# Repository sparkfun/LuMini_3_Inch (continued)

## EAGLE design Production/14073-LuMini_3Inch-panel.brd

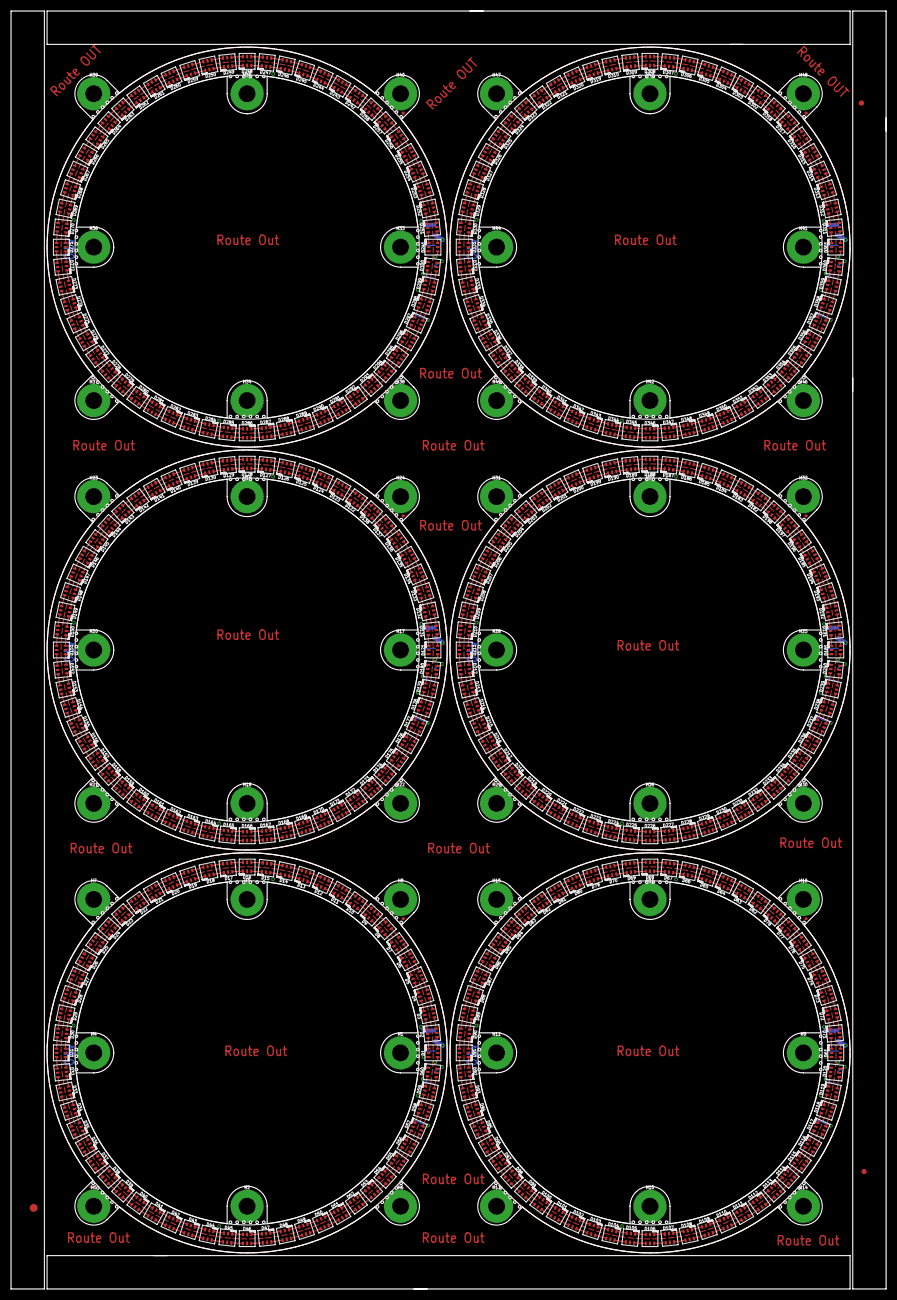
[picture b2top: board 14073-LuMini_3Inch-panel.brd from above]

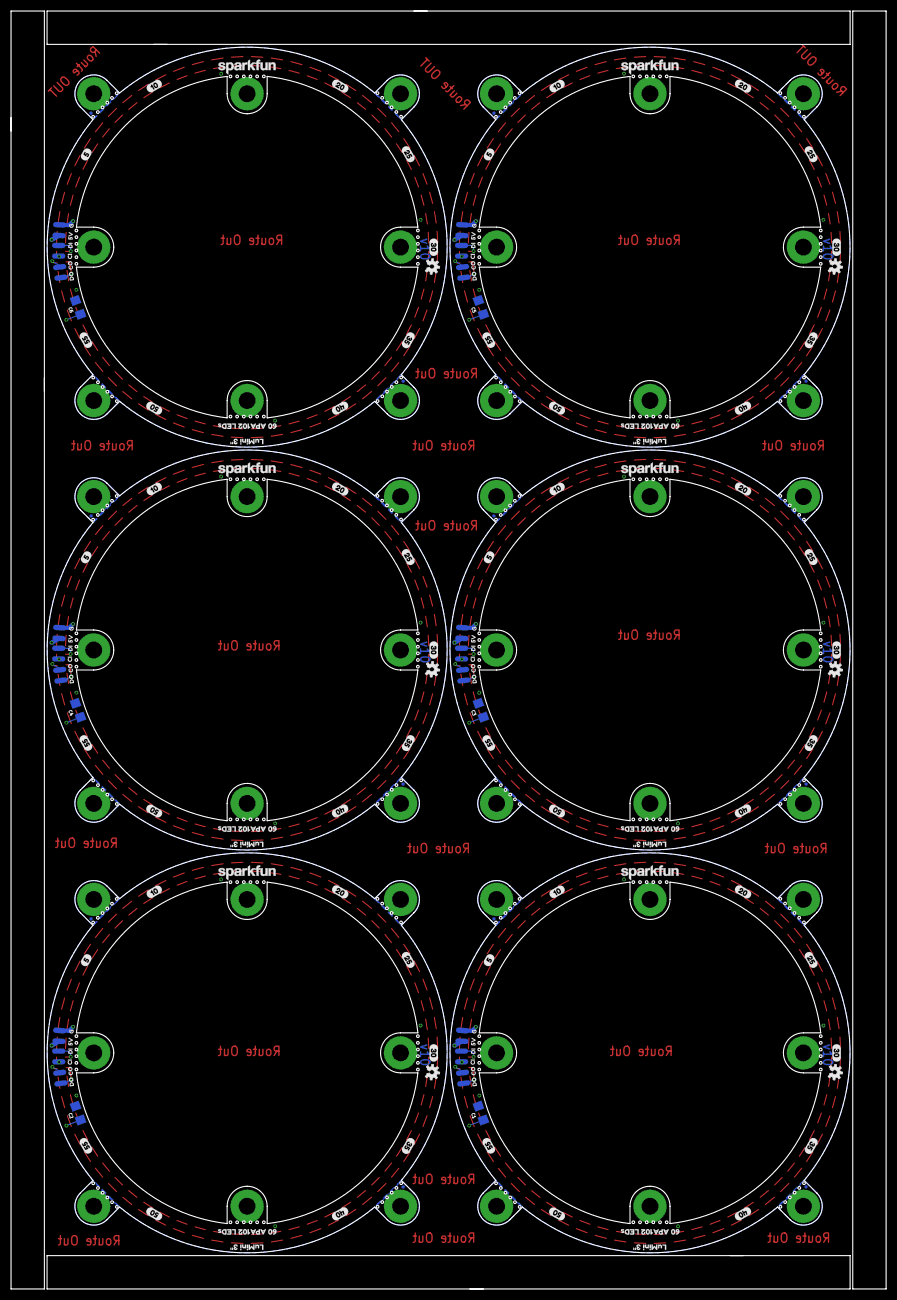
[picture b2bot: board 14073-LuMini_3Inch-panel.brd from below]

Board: 2 copper layers, 166.6 x 243.3 mm, 573 parts (150 on the bottom side), 744 nets.

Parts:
C1, C2, C3, C4, C5, C6: DNP; 1206
D1, D2, D3, D4, D5, D6, D7, D8, D9, D10, D11, D12, D13, D14, D15, D16, D17, D18, D19, D20, D21, D22, D23, D24, D25, D26, D27, D28, D29, D30, D31, D32, D33, D34, D35, D36, D37, D38, D39, D40, D41, D42, D43, D44, D45, D46, D47, D48, D49, D50, D51, D52, D53, D54, D55, D56, D57, D58, D59, D60, D61, D62, D63, D64, D65, D66, D67, D68, D69, D70, D71, D72, D73, D74, D75, D76, D77, D78, D79, D80, D81, D82, D83, D84, D85, D86, D87, D88, D89, D90, D91, D92, D93, D94, D95, D96, D97, D98, D99, D100, D101, D102, D103, D104, D105, D106, D107, D108, D109, D110, D111, D112, D113, D114, D115, D116, D117, D118, D119, D120, D121, D122, D123, D124, D125, D126, D127, D128, D129, D130, D131, D132, D133, D134, D135, D136, D137, D138, D139, D140, D141, D142, D143, D144, D145, D146, D147, D148, D149, D150, D151, D152, D153, D154, D155, D156, D157, D158, D159, D160, D161, D162, D163, D164, D165, D166, D167, D168, D169, D170, D171, D172, D173, D174, D175, D176, D177, D178, D179, D180, D181, D182, D183, D184, D185, D186, D187, D188, D189, D190, D191, D192, D193, D194, D195, D196, D197, D198, D199, D200, D201, D202, D203, D204, D205, D206, D207, D208, D209, D210, D211, D212, D213, D214, D215, D216, D217, D218, D219, D220, D221, D222, D223, D224, D225, D226, D227, D228, D229, D230, D231, D232, D233, D234, D235, D236, D237, D238, D239, D240, D241, D242, D243, D244, D245, D246, D247, D248, D249, D250, D251, D252, D253, D254, D255, D256, D257, D258, D259, D260, D261, D262, D263, D264, D265, D266, D267, D268, D269, D270, D271, D272, D273, D274, D275, D276, D277, D278, D279, D280, D281, D282, D283, D284, D285, D286, D287, D288, D289, D290, D291, D292, D293, D294, D295, D296, D297, D298, D299, D300, D301, D302, D303, D304, D305, D306, D307, D308, D309, D310, D311, D312, D313, D314, D315, D316, D317, D318, D319, D320, D321, D322, D323, D324, D325, D326, D327, D328, D329, D330, D331, D332, D333, D334, D335, D336, D337, D338, D339, D340, D341, D342, D343, D344, D345, D346, D347, D348, D349, D350, D351, D352, D353, D354, D355, D356, D357, D358, D359, D360: APA102-2020
E$6: FIDUCIAL-1.5X3
E$7, E$8: FIDUCIAL-1X2
FD1, FD2, FD3, FD4, FD5, FD6, FD7, FD8, FD9, FD10, FD11, FD12, FD13, FD14, FD15, FD16, FD17, FD18, FD19, FD20, FD21, FD22, FD23, FD24: FIDUCIALUFIDUCIAL; FIDUCIAL-MICRO
H1, H2, H3, H4, H5, H6, H7, H8, H9, H10, H11, H12, H13, H14, H15, H16, H17, H18, H19, H20, H21, H22, H23, H24, H25, H26, H27, H28, H29, H30, H31, H32, H33, H34, H35, H36, H37, H38, H39, H40, H41, H42, H43, H44, H45, H46, H47, H48: STANDOFF_ELECTRICAL-NOTHERMALS; STANDOFF-ELECTRICAL-NOTHERMALS
J1, J2, J3, J4, J5, J6, J7, J8, J9, J10, J11, J12, J13, J14, J15, J16, J17, J18: SOLDER_PAD_2
LOGO1, LOGO3, LOGO5, LOGO7, LOGO9, LOGO11: OSHW-LOGOS; OSHW-LOGO-S
LOGO2, LOGO4, LOGO6, LOGO8, LOGO10, LOGO12: SFE_LOGO_NAME.1_INCH; SFE_LOGO_NAME_.1
U$1, U$18, U$35, U$52, U$69, U$86: LUMINI_3#2
U$2, U$25, U$42, U$59, U$76, U$93: 60_APA102_LEDS0
U$3, U$26, U$43, U$60, U$77, U$94: 54
U$4, U$19, U$36, U$53, U$70, U$87: 5V6
U$5, U$20, U$37, U$54, U$71, U$88: G4
U$6, U$27, U$44, U$61, U$78, U$95: 105
U$7, U$21, U$38, U$55, U$72, U$89: DO3
U$8, U$22, U$39, U$56, U$73, U$90: CO1
U$9, U$23, U$40, U$57, U$74, U$91: CI6
U$10, U$24, U$41, U$58, U$75, U$92: DI4
U$11, U$28, U$45, U$62, U$79, U$96: 207
U$12, U$29, U$46, U$63, U$80, U$97: 258
U$13, U$30, U$47, U$64, U$81, U$98: 309
U$14, U$31, U$48, U$65, U$82, U$99: 3510
U$15, U$32, U$49, U$66, U$83, U$100: 4011
U$16, U$33, U$50, U$67, U$84, U$101: 5013
U$17, U$34, U$51, U$68, U$85, U$102: 5514

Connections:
5V: C1.1, D1.VDD, D2.VDD, D3.VDD, D4.VDD, D5.VDD, D6.VDD, D7.VDD, D8.VDD, D9.VDD, D10.VDD, D11.VDD, D12.VDD, D13.VDD, D14.VDD, D15.VDD, D16.VDD, D17.VDD, D18.VDD, D19.VDD, D20.VDD, D21.VDD, D22.VDD, D23.VDD, D24.VDD, D25.VDD, D26.VDD, D27.VDD, D28.VDD, D29.VDD, D30.VDD, D31.VDD, D32.VDD, D33.VDD, D34.VDD, D35.VDD, D36.VDD, D37.VDD, D38.VDD, D39.VDD, D40.VDD, D41.VDD, D42.VDD, D43.VDD, D44.VDD, D45.VDD, D46.VDD, D47.VDD, D48.VDD, D49.VDD, D50.VDD, D51.VDD, D52.VDD, D53.VDD, D54.VDD, D55.VDD, D56.VDD, D57.VDD, D58.VDD, D59.VDD, D60.VDD, J1.P$2
5V1: C2.1, D61.VDD, D62.VDD, D63.VDD, D64.VDD, D65.VDD, D66.VDD, D67.VDD, D68.VDD, D69.VDD, D70.VDD, D71.VDD, D72.VDD, D73.VDD, D74.VDD, D75.VDD, D76.VDD, D77.VDD, D78.VDD, D79.VDD, D80.VDD, D81.VDD, D82.VDD, D83.VDD, D84.VDD, D85.VDD, D86.VDD, D87.VDD, D88.VDD, D89.VDD, D90.VDD, D91.VDD, D92.VDD, D93.VDD, D94.VDD, D95.VDD, D96.VDD, D97.VDD, D98.VDD, D99.VDD, D100.VDD, D101.VDD, D102.VDD, D103.VDD, D104.VDD, D105.VDD, D106.VDD, D107.VDD, D108.VDD, D109.VDD, D110.VDD, D111.VDD, D112.VDD, D113.VDD, D114.VDD, D115.VDD, D116.VDD, D117.VDD, D118.VDD, D119.VDD, D120.VDD, J4.P$2
5V2: C3.1, D121.VDD, D122.VDD, D123.VDD, D124.VDD, D125.VDD, D126.VDD, D127.VDD, D128.VDD, D129.VDD, D130.VDD, D131.VDD, D132.VDD, D133.VDD, D134.VDD, D135.VDD, D136.VDD, D137.VDD, D138.VDD, D139.VDD, D140.VDD, D141.VDD, D142.VDD, D143.VDD, D144.VDD, D145.VDD, D146.VDD, D147.VDD, D148.VDD, D149.VDD, D150.VDD, D151.VDD, D152.VDD, D153.VDD, D154.VDD, D155.VDD, D156.VDD, D157.VDD, D158.VDD, D159.VDD, D160.VDD, D161.VDD, D162.VDD, D163.VDD, D164.VDD, D165.VDD, D166.VDD, D167.VDD, D168.VDD, D169.VDD, D170.VDD, D171.VDD, D172.VDD, D173.VDD, D174.VDD, D175.VDD, D176.VDD, D177.VDD, D178.VDD, D179.VDD, D180.VDD, J7.P$2
5V3: C4.1, D181.VDD, D182.VDD, D183.VDD, D184.VDD, D185.VDD, D186.VDD, D187.VDD, D188.VDD, D189.VDD, D190.VDD, D191.VDD, D192.VDD, D193.VDD, D194.VDD, D195.VDD, D196.VDD, D197.VDD, D198.VDD, D199.VDD, D200.VDD, D201.VDD, D202.VDD, D203.VDD, D204.VDD, D205.VDD, D206.VDD, D207.VDD, D208.VDD, D209.VDD, D210.VDD, D211.VDD, D212.VDD, D213.VDD, D214.VDD, D215.VDD, D216.VDD, D217.VDD, D218.VDD, D219.VDD, D220.VDD, D221.VDD, D222.VDD, D223.VDD, D224.VDD, D225.VDD, D226.VDD, D227.VDD, D228.VDD, D229.VDD, D230.VDD, D231.VDD, D232.VDD, D233.VDD, D234.VDD, D235.VDD, D236.VDD, D237.VDD, D238.VDD, D239.VDD, D240.VDD, J10.P$2
5V4: C5.1, D241.VDD, D242.VDD, D243.VDD, D244.VDD, D245.VDD, D246.VDD, D247.VDD, D248.VDD, D249.VDD, D250.VDD, D251.VDD, D252.VDD, D253.VDD, D254.VDD, D255.VDD, D256.VDD, D257.VDD, D258.VDD, D259.VDD, D260.VDD, D261.VDD, D262.VDD, D263.VDD, D264.VDD, D265.VDD, D266.VDD, D267.VDD, D268.VDD, D269.VDD, D270.VDD, D271.VDD, D272.VDD, D273.VDD, D274.VDD, D275.VDD, D276.VDD, D277.VDD, D278.VDD, D279.VDD, D280.VDD, D281.VDD, D282.VDD, D283.VDD, D284.VDD, D285.VDD, D286.VDD, D287.VDD, D288.VDD, D289.VDD, D290.VDD, D291.VDD, D292.VDD, D293.VDD, D294.VDD, D295.VDD, D296.VDD, D297.VDD, D298.VDD, D299.VDD, D300.VDD, J13.P$2
5V5: C6.1, D301.VDD, D302.VDD, D303.VDD, D304.VDD, D305.VDD, D306.VDD, D307.VDD, D308.VDD, D309.VDD, D310.VDD, D311.VDD, D312.VDD, D313.VDD, D314.VDD, D315.VDD, D316.VDD, D317.VDD, D318.VDD, D319.VDD, D320.VDD, D321.VDD, D322.VDD, D323.VDD, D324.VDD, D325.VDD, D326.VDD, D327.VDD, D328.VDD, D329.VDD, D330.VDD, D331.VDD, D332.VDD, D333.VDD, D334.VDD, D335.VDD, D336.VDD, D337.VDD, D338.VDD, D339.VDD, D340.VDD, D341.VDD, D342.VDD, D343.VDD, D344.VDD, D345.VDD, D346.VDD, D347.VDD, D348.VDD, D349.VDD, D350.VDD, D351.VDD, D352.VDD, D353.VDD, D354.VDD, D355.VDD, D356.VDD, D357.VDD, D358.VDD, D359.VDD, D360.VDD, J16.P$2
CI: D1.CKI, J2.P$2
CI1: D61.CKI, J5.P$2
CI2: D121.CKI, J8.P$2
CI3: D181.CKI, J11.P$2
CI4: D241.CKI, J14.P$2
CI5: D301.CKI, J17.P$2
CO: D60.CKO, J3.P$2
CO1: D120.CKO, J6.P$2
CO2: D180.CKO, J9.P$2
CO3: D240.CKO, J12.P$2
CO4: D300.CKO, J15.P$2
CO5: D360.CKO, J18.P$2
DI: D1.SDI, J2.P$1
DI1: D61.SDI, J5.P$1
DI2: D121.SDI, J8.P$1
DI3: D181.SDI, J11.P$1
DI4: D241.SDI, J14.P$1
DI5: D301.SDI, J17.P$1
DO: D60.SDO, J3.P$1
DO1: D120.SDO, J6.P$1
DO2: D180.SDO, J9.P$1
DO3: D240.SDO, J12.P$1
DO4: D300.SDO, J15.P$1
DO5: D360.SDO, J18.P$1
GND: C1.2, D1.GND, D2.GND, D3.GND, D4.GND, D5.GND, D6.GND, D7.GND, D8.GND, D9.GND, D10.GND, D11.GND, D12.GND, D13.GND, D14.GND, D15.GND, D16.GND, D17.GND, D18.GND, D19.GND, D20.GND, D21.GND, D22.GND, D23.GND, D24.GND, D25.GND, D26.GND, D27.GND, D28.GND, D29.GND, D30.GND, D31.GND, D32.GND, D33.GND, D34.GND, D35.GND, D36.GND, D37.GND, D38.GND, D39.GND, D40.GND, D41.GND, D42.GND, D43.GND, D44.GND, D45.GND, D46.GND, D47.GND, D48.GND, D49.GND, D50.GND, D51.GND, D52.GND, D53.GND, D54.GND, D55.GND, D56.GND, D57.GND, D58.GND, D59.GND, D60.GND, H1.P1, H2.P1, H3.P1, H4.P1, H5.P1, H6.P1, H7.P1, H8.P1, J1.P$1
GND1: C2.2, D61.GND, D62.GND, D63.GND, D64.GND, D65.GND, D66.GND, D67.GND, D68.GND, D69.GND, D70.GND, D71.GND, D72.GND, D73.GND, D74.GND, D75.GND, D76.GND, D77.GND, D78.GND, D79.GND, D80.GND, D81.GND, D82.GND, D83.GND, D84.GND, D85.GND, D86.GND, D87.GND, D88.GND, D89.GND, D90.GND, D91.GND, D92.GND, D93.GND, D94.GND, D95.GND, D96.GND, D97.GND, D98.GND, D99.GND, D100.GND, D101.GND, D102.GND, D103.GND, D104.GND, D105.GND, D106.GND, D107.GND, D108.GND, D109.GND, D110.GND, D111.GND, D112.GND, D113.GND, D114.GND, D115.GND, D116.GND, D117.GND, D118.GND, D119.GND, D120.GND, H9.P1, H10.P1, H11.P1, H12.P1, H13.P1, H14.P1, H15.P1, H16.P1, J4.P$1
GND2: C3.2, D121.GND, D122.GND, D123.GND, D124.GND, D125.GND, D126.GND, D127.GND, D128.GND, D129.GND, D130.GND, D131.GND, D132.GND, D133.GND, D134.GND, D135.GND, D136.GND, D137.GND, D138.GND, D139.GND, D140.GND, D141.GND, D142.GND, D143.GND, D144.GND, D145.GND, D146.GND, D147.GND, D148.GND, D149.GND, D150.GND, D151.GND, D152.GND, D153.GND, D154.GND, D155.GND, D156.GND, D157.GND, D158.GND, D159.GND, D160.GND, D161.GND, D162.GND, D163.GND, D164.GND, D165.GND, D166.GND, D167.GND, D168.GND, D169.GND, D170.GND, D171.GND, D172.GND, D173.GND, D174.GND, D175.GND, D176.GND, D177.GND, D178.GND, D179.GND, D180.GND, H17.P1, H18.P1, H19.P1, H20.P1, H21.P1, H22.P1, H23.P1, H24.P1, J7.P$1
GND3: C4.2, D181.GND, D182.GND, D183.GND, D184.GND, D185.GND, D186.GND, D187.GND, D188.GND, D189.GND, D190.GND, D191.GND, D192.GND, D193.GND, D194.GND, D195.GND, D196.GND, D197.GND, D198.GND, D199.GND, D200.GND, D201.GND, D202.GND, D203.GND, D204.GND, D205.GND, D206.GND, D207.GND, D208.GND, D209.GND, D210.GND, D211.GND, D212.GND, D213.GND, D214.GND, D215.GND, D216.GND, D217.GND, D218.GND, D219.GND, D220.GND, D221.GND, D222.GND, D223.GND, D224.GND, D225.GND, D226.GND, D227.GND, D228.GND, D229.GND, D230.GND, D231.GND, D232.GND, D233.GND, D234.GND, D235.GND, D236.GND, D237.GND, D238.GND, D239.GND, D240.GND, H25.P1, H26.P1, H27.P1, H28.P1, H29.P1, H30.P1, H31.P1, H32.P1, J10.P$1
GND4: C5.2, D241.GND, D242.GND, D243.GND, D244.GND, D245.GND, D246.GND, D247.GND, D248.GND, D249.GND, D250.GND, D251.GND, D252.GND, D253.GND, D254.GND, D255.GND, D256.GND, D257.GND, D258.GND, D259.GND, D260.GND, D261.GND, D262.GND, D263.GND, D264.GND, D265.GND, D266.GND, D267.GND, D268.GND, D269.GND, D270.GND, D271.GND, D272.GND, D273.GND, D274.GND, D275.GND, D276.GND, D277.GND, D278.GND, D279.GND, D280.GND, D281.GND, D282.GND, D283.GND, D284.GND, D285.GND, D286.GND, D287.GND, D288.GND, D289.GND, D290.GND, D291.GND, D292.GND, D293.GND, D294.GND, D295.GND, D296.GND, D297.GND, D298.GND, D299.GND, D300.GND, H33.P1, H34.P1, H35.P1, H36.P1, H37.P1, H38.P1, H39.P1, H40.P1, J13.P$1
GND5: C6.2, D301.GND, D302.GND, D303.GND, D304.GND, D305.GND, D306.GND, D307.GND, D308.GND, D309.GND, D310.GND, D311.GND, D312.GND, D313.GND, D314.GND, D315.GND, D316.GND, D317.GND, D318.GND, D319.GND, D320.GND, D321.GND, D322.GND, D323.GND, D324.GND, D325.GND, D326.GND, D327.GND, D328.GND, D329.GND, D330.GND, D331.GND, D332.GND, D333.GND, D334.GND, D335.GND, D336.GND, D337.GND, D338.GND, D339.GND, D340.GND, D341.GND, D342.GND, D343.GND, D344.GND, D345.GND, D346.GND, D347.GND, D348.GND, D349.GND, D350.GND, D351.GND, D352.GND, D353.GND, D354.GND, D355.GND, D356.GND, D357.GND, D358.GND, D359.GND, D360.GND, H41.P1, H42.P1, H43.P1, H44.P1, H45.P1, H46.P1, H47.P1, H48.P1, J16.P$1
unnamed: D4.CKO, D5.CKI
unnamed: D61.CKO, D71.CKI
unnamed: D61.SDO, D71.SDI
unnamed: D1.CKO, D2.CKI
unnamed: D1.SDO, D2.SDI
unnamed: D2.CKO, D3.CKI
unnamed: D2.SDO, D3.SDI
unnamed: D3.CKO, D4.CKI
unnamed: D3.SDO, D4.SDI
unnamed: D4.SDO, D5.SDI
unnamed: D5.CKO, D6.CKI
unnamed: D5.SDO, D6.SDI
unnamed: D6.CKO, D7.CKI
unnamed: D6.SDO, D7.SDI
unnamed: D7.CKO, D8.CKI
unnamed: D7.SDO, D8.SDI
unnamed: D16.SDO, D17.SDI
unnamed: D20.SDO, D21.SDI
unnamed: D9.CKO, D10.CKI
unnamed: D9.SDO, D10.SDI
unnamed: D10.CKO, D11.CKI
unnamed: D10.SDO, D11.SDI
unnamed: D11.CKO, D12.CKI
unnamed: D11.SDO, D12.SDI
unnamed: D12.CKO, D13.CKI
unnamed: D12.SDO, D13.SDI
unnamed: D13.CKO, D14.CKI
unnamed: D13.SDO, D14.SDI
unnamed: D14.CKO, D15.CKI
unnamed: D14.SDO, D15.SDI
unnamed: D45.CKO, D46.CKI
unnamed: D30.CKO, D31.CKI
unnamed: D8.CKO, D9.CKI
unnamed: D8.SDO, D9.SDI
unnamed: D17.CKO, D18.CKI
unnamed: D17.SDO, D18.SDI
unnamed: D18.CKO, D19.CKI
unnamed: D18.SDO, D19.SDI
unnamed: D19.CKO, D20.CKI
unnamed: D19.SDO, D20.SDI
unnamed: D30.SDO, D31.SDI
unnamed: D15.CKO, D16.CKI
unnamed: D16.CKO, D17.CKI
unnamed: D21.CKO, D22.CKI
unnamed: D21.SDO, D22.SDI
unnamed: D22.CKO, D23.CKI
unnamed: D22.SDO, D23.SDI
unnamed: D23.CKO, D24.CKI
unnamed: D23.SDO, D24.SDI
unnamed: D24.CKO, D25.CKI
unnamed: D24.SDO, D25.SDI
unnamed: D25.CKO, D26.CKI
unnamed: D25.SDO, D26.SDI
unnamed: D26.CKO, D27.CKI
unnamed: D26.SDO, D27.SDI
unnamed: D27.CKO, D28.CKI
unnamed: D27.SDO, D28.SDI
unnamed: D29.CKO, D30.CKI
unnamed: D29.SDO, D30.SDI
unnamed: D15.SDO, D16.SDI
unnamed: D45.SDO, D46.SDI
unnamed: D31.CKO, D32.CKI
unnamed: D31.SDO, D32.SDI
unnamed: D32.CKO, D33.CKI
unnamed: D32.SDO, D33.SDI
unnamed: D33.CKO, D34.CKI
unnamed: D33.SDO, D34.SDI
unnamed: D34.CKO, D35.CKI
unnamed: D34.SDO, D35.SDI
unnamed: D35.CKO, D36.CKI
unnamed: D35.SDO, D36.SDI
unnamed: D37.CKO, D38.CKI
unnamed: D37.SDO, D38.SDI
unnamed: D38.SDO, D39.SDI
unnamed: D39.CKO, D40.CKI
unnamed: D39.SDO, D40.SDI
unnamed: D38.CKO, D39.CKI
unnamed: D28.CKO, D29.CKI
unnamed: D28.SDO, D29.SDI
unnamed: D36.SDO, D37.SDI
unnamed: D36.CKO, D37.CKI
unnamed: D40.CKO, D41.CKI
unnamed: D40.SDO, D41.SDI
unnamed: D41.CKO, D42.CKI
unnamed: D41.SDO, D42.SDI
unnamed: D42.CKO, D43.CKI
unnamed: D42.SDO, D43.SDI
unnamed: D43.CKO, D44.CKI
unnamed: D43.SDO, D44.SDI
unnamed: D44.CKO, D45.CKI
unnamed: D44.SDO, D45.SDI
unnamed: D71.CKO, D72.CKI
unnamed: D71.SDO, D72.SDI
unnamed: D46.CKO, D47.CKI
unnamed: D46.SDO, D47.SDI
unnamed: D47.CKO, D48.CKI
unnamed: D47.SDO, D48.SDI
unnamed: D49.CKO, D50.CKI
unnamed: D49.SDO, D50.SDI
unnamed: D50.CKO, D51.CKI
unnamed: D50.SDO, D51.SDI
unnamed: D51.CKO, D52.CKI
unnamed: D51.SDO, D52.SDI
unnamed: D52.CKO, D53.CKI
unnamed: D52.SDO, D53.SDI
unnamed: D53.CKO, D54.CKI
unnamed: D53.SDO, D54.SDI
unnamed: D54.CKO, D55.CKI
unnamed: D54.SDO, D55.SDI
unnamed: D55.CKO, D56.CKI
unnamed: D55.SDO, D56.SDI
unnamed: D57.CKO, D58.CKI
unnamed: D57.SDO, D58.SDI
unnamed: D58.SDO, D59.SDI
unnamed: D59.CKO, D60.CKI
unnamed: D59.SDO, D60.SDI
unnamed: D58.CKO, D59.CKI
unnamed: D48.CKO, D49.CKI
unnamed: D48.SDO, D49.SDI
unnamed: D56.SDO, D57.SDI
unnamed: D56.CKO, D57.CKI
unnamed: D72.CKO, D73.CKI
unnamed: D72.SDO, D73.SDI
unnamed: D20.CKO, D21.CKI
unnamed: D73.CKO, D74.CKI
unnamed: D73.SDO, D74.SDI
unnamed: D74.CKO, D75.CKI
unnamed: D74.SDO, D75.SDI
unnamed: D75.CKO, D76.CKI
unnamed: D75.SDO, D76.SDI
unnamed: D76.CKO, D77.CKI
unnamed: D76.SDO, D77.SDI
unnamed: D62.CKI, D78.CKO
unnamed: D62.SDI, D78.SDO
unnamed: D62.CKO, D63.CKI
unnamed: D62.SDO, D63.SDI
unnamed: D63.CKO, D64.CKI
unnamed: D63.SDO, D64.SDI
unnamed: D64.CKO, D65.CKI
unnamed: D64.SDO, D65.SDI
unnamed: D65.CKO, D66.CKI
unnamed: D65.SDO, D66.SDI
unnamed: D66.CKO, D67.CKI
unnamed: D66.SDO, D67.SDI
unnamed: D69.CKO, D70.CKI
unnamed: D69.SDO, D70.SDI
unnamed: D70.SDO, D79.SDI
unnamed: D79.CKO, D80.CKI
unnamed: D79.SDO, D80.SDI
unnamed: D70.CKO, D79.CKI
unnamed: D77.CKO, D78.CKI
unnamed: D77.SDO, D78.SDI
unnamed: D68.SDO, D69.SDI
unnamed: D68.CKO, D69.CKI
unnamed: D81.CKO, D82.CKI
unnamed: D81.SDO, D82.SDI
unnamed: D82.CKO, D83.CKI
unnamed: D82.SDO, D83.SDI
unnamed: D83.CKO, D84.CKI
unnamed: D83.SDO, D84.SDI
unnamed: D84.CKO, D85.CKI
unnamed: D84.SDO, D85.SDI
unnamed: D85.CKO, D86.CKI
unnamed: D85.SDO, D86.SDI
unnamed: D86.CKO, D87.CKI
unnamed: D86.SDO, D87.SDI
unnamed: D87.CKO, D88.CKI
unnamed: D87.SDO, D88.SDI
unnamed: D89.CKO, D90.CKI
unnamed: D89.SDO, D90.SDI
unnamed: D91.CKO, D92.CKI
unnamed: D91.SDO, D92.SDI
unnamed: D92.CKO, D93.CKI
unnamed: D92.SDO, D93.SDI
unnamed: D93.CKO, D94.CKI
unnamed: D93.SDO, D94.SDI
unnamed: D94.CKO, D95.CKI
unnamed: D94.SDO, D95.SDI
unnamed: D95.CKO, D96.CKI
unnamed: D95.SDO, D96.SDI
unnamed: D97.CKO, D98.CKI
unnamed: D97.SDO, D98.SDI
unnamed: D98.SDO, D99.SDI
unnamed: D99.CKO, D100.CKI
unnamed: D99.SDO, D100.SDI
unnamed: D98.CKO, D99.CKI
unnamed: D88.CKO, D89.CKI
unnamed: D88.SDO, D89.SDI
unnamed: D96.SDO, D97.SDI
unnamed: D96.CKO, D97.CKI
unnamed: D101.CKO, D102.CKI
unnamed: D101.SDO, D102.SDI
unnamed: D102.CKO, D103.CKI
unnamed: D102.SDO, D103.SDI
unnamed: D103.CKO, D104.CKI
unnamed: D103.SDO, D104.SDI
unnamed: D104.CKO, D105.CKI
unnamed: D104.SDO, D105.SDI
unnamed: D106.CKO, D107.CKI
unnamed: D106.SDO, D107.SDI
unnamed: D107.CKO, D108.CKI
unnamed: D107.SDO, D108.SDI
unnamed: D109.CKO, D110.CKI
unnamed: D109.SDO, D110.SDI
unnamed: D110.CKO, D111.CKI
unnamed: D110.SDO, D111.SDI
unnamed: D111.CKO, D112.CKI
unnamed: D111.SDO, D112.SDI
unnamed: D112.CKO, D113.CKI
unnamed: D112.SDO, D113.SDI
unnamed: D113.CKO, D114.CKI
unnamed: D113.SDO, D114.SDI
unnamed: D114.CKO, D115.CKI
unnamed: D114.SDO, D115.SDI
unnamed: D115.CKO, D116.CKI
unnamed: D115.SDO, D116.SDI
unnamed: D117.CKO, D118.CKI
unnamed: D117.SDO, D118.SDI
unnamed: D118.SDO, D119.SDI
unnamed: D119.CKO, D120.CKI
unnamed: D119.SDO, D120.SDI
unnamed: D118.CKO, D119.CKI
unnamed: D108.CKO, D109.CKI
unnamed: D108.SDO, D109.SDI
unnamed: D116.SDO, D117.SDI
unnamed: D116.CKO, D117.CKI
unnamed: D80.CKO, D81.CKI
unnamed: D80.SDO, D81.SDI
unnamed: D105.CKO, D106.CKI
unnamed: D90.CKO, D91.CKI
unnamed: D90.SDO, D91.SDI
unnamed: D67.CKO, D68.CKI
unnamed: D67.SDO, D68.SDI
unnamed: D105.SDO, D106.SDI
unnamed: D100.CKO, D101.CKI
unnamed: D100.SDO, D101.SDI
unnamed: D121.CKO, D131.CKI
unnamed: D121.SDO, D131.SDI
unnamed: D131.CKO, D132.CKI
unnamed: D131.SDO, D132.SDI
unnamed: D132.CKO, D133.CKI
unnamed: D132.SDO, D133.SDI
unnamed: D133.CKO, D134.CKI
unnamed: D133.SDO, D134.SDI
unnamed: D134.CKO, D135.CKI
unnamed: D134.SDO, D135.SDI
unnamed: D135.CKO, D136.CKI
unnamed: D135.SDO, D136.SDI
unnamed: D136.CKO, D137.CKI
unnamed: D136.SDO, D137.SDI
unnamed: D122.CKI, D138.CKO
unnamed: D122.SDI, D138.SDO
unnamed: D122.CKO, D123.CKI
unnamed: D122.SDO, D123.SDI
unnamed: D123.CKO, D124.CKI
unnamed: D123.SDO, D124.SDI
unnamed: D124.CKO, D125.CKI
unnamed: D124.SDO, D125.SDI
unnamed: D125.CKO, D126.CKI
unnamed: D125.SDO, D126.SDI
unnamed: D126.CKO, D127.CKI
unnamed: D126.SDO, D127.SDI
unnamed: D129.CKO, D130.CKI
unnamed: D129.SDO, D130.SDI
unnamed: D130.SDO, D139.SDI
unnamed: D139.CKO, D140.CKI
unnamed: D139.SDO, D140.SDI
unnamed: D130.CKO, D139.CKI
unnamed: D137.CKO, D138.CKI
unnamed: D137.SDO, D138.SDI
unnamed: D128.SDO, D129.SDI
unnamed: D128.CKO, D129.CKI
unnamed: D141.CKO, D142.CKI
unnamed: D141.SDO, D142.SDI
unnamed: D142.CKO, D143.CKI
unnamed: D142.SDO, D143.SDI
unnamed: D143.CKO, D144.CKI
unnamed: D143.SDO, D144.SDI
unnamed: D144.CKO, D145.CKI
unnamed: D144.SDO, D145.SDI
unnamed: D145.CKO, D146.CKI
unnamed: D145.SDO, D146.SDI
unnamed: D146.CKO, D147.CKI
unnamed: D146.SDO, D147.SDI
unnamed: D147.CKO, D148.CKI
unnamed: D147.SDO, D148.SDI
unnamed: D149.CKO, D150.CKI
unnamed: D149.SDO, D150.SDI
unnamed: D151.CKO, D152.CKI
unnamed: D151.SDO, D152.SDI
unnamed: D152.CKO, D153.CKI
unnamed: D152.SDO, D153.SDI
unnamed: D153.CKO, D154.CKI
unnamed: D153.SDO, D154.SDI
unnamed: D154.CKO, D155.CKI
unnamed: D154.SDO, D155.SDI
unnamed: D155.CKO, D156.CKI
unnamed: D155.SDO, D156.SDI
unnamed: D157.CKO, D158.CKI
unnamed: D157.SDO, D158.SDI
unnamed: D158.SDO, D159.SDI
unnamed: D159.CKO, D160.CKI
unnamed: D159.SDO, D160.SDI
unnamed: D158.CKO, D159.CKI
unnamed: D148.CKO, D149.CKI
unnamed: D148.SDO, D149.SDI
unnamed: D156.SDO, D157.SDI
unnamed: D156.CKO, D157.CKI
unnamed: D161.CKO, D162.CKI
unnamed: D161.SDO, D162.SDI
unnamed: D162.CKO, D163.CKI
unnamed: D162.SDO, D163.SDI
unnamed: D163.CKO, D164.CKI
unnamed: D163.SDO, D164.SDI
unnamed: D164.CKO, D165.CKI
unnamed: D164.SDO, D165.SDI
unnamed: D166.CKO, D167.CKI
unnamed: D166.SDO, D167.SDI
unnamed: D167.CKO, D168.CKI
unnamed: D167.SDO, D168.SDI
unnamed: D169.CKO, D170.CKI
unnamed: D169.SDO, D170.SDI
unnamed: D170.CKO, D171.CKI
unnamed: D170.SDO, D171.SDI
unnamed: D171.CKO, D172.CKI
unnamed: D171.SDO, D172.SDI
unnamed: D172.CKO, D173.CKI
unnamed: D172.SDO, D173.SDI
unnamed: D173.CKO, D174.CKI
unnamed: D173.SDO, D174.SDI
unnamed: D174.CKO, D175.CKI
unnamed: D174.SDO, D175.SDI
unnamed: D175.CKO, D176.CKI
unnamed: D175.SDO, D176.SDI
unnamed: D177.CKO, D178.CKI
unnamed: D177.SDO, D178.SDI
unnamed: D178.SDO, D179.SDI
unnamed: D179.CKO, D180.CKI
unnamed: D179.SDO, D180.SDI
unnamed: D178.CKO, D179.CKI
unnamed: D168.CKO, D169.CKI
unnamed: D168.SDO, D169.SDI
unnamed: D176.SDO, D177.SDI
unnamed: D176.CKO, D177.CKI
unnamed: D140.CKO, D141.CKI
unnamed: D140.SDO, D141.SDI
unnamed: D165.CKO, D166.CKI
unnamed: D150.CKO, D151.CKI
unnamed: D150.SDO, D151.SDI
unnamed: D127.CKO, D128.CKI
unnamed: D127.SDO, D128.SDI
unnamed: D165.SDO, D166.SDI
unnamed: D160.CKO, D161.CKI
unnamed: D160.SDO, D161.SDI
unnamed: D181.CKO, D191.CKI
unnamed: D181.SDO, D191.SDI
unnamed: D191.CKO, D192.CKI
unnamed: D191.SDO, D192.SDI
unnamed: D192.CKO, D193.CKI
unnamed: D192.SDO, D193.SDI
unnamed: D193.CKO, D194.CKI
unnamed: D193.SDO, D194.SDI
unnamed: D194.CKO, D195.CKI
unnamed: D194.SDO, D195.SDI
unnamed: D195.CKO, D196.CKI
unnamed: D195.SDO, D196.SDI
unnamed: D196.CKO, D197.CKI
unnamed: D196.SDO, D197.SDI
unnamed: D182.CKI, D198.CKO
unnamed: D182.SDI, D198.SDO
unnamed: D182.CKO, D183.CKI
unnamed: D182.SDO, D183.SDI
unnamed: D183.CKO, D184.CKI
unnamed: D183.SDO, D184.SDI
unnamed: D184.CKO, D185.CKI
unnamed: D184.SDO, D185.SDI
unnamed: D185.CKO, D186.CKI
unnamed: D185.SDO, D186.SDI
unnamed: D186.CKO, D187.CKI
unnamed: D186.SDO, D187.SDI
unnamed: D189.CKO, D190.CKI
unnamed: D189.SDO, D190.SDI
unnamed: D190.SDO, D199.SDI
unnamed: D199.CKO, D200.CKI
unnamed: D199.SDO, D200.SDI
unnamed: D190.CKO, D199.CKI
unnamed: D197.CKO, D198.CKI
unnamed: D197.SDO, D198.SDI
unnamed: D188.SDO, D189.SDI
unnamed: D188.CKO, D189.CKI
unnamed: D201.CKO, D202.CKI
unnamed: D201.SDO, D202.SDI
unnamed: D202.CKO, D203.CKI
unnamed: D202.SDO, D203.SDI
unnamed: D203.CKO, D204.CKI
unnamed: D203.SDO, D204.SDI
unnamed: D204.CKO, D205.CKI
unnamed: D204.SDO, D205.SDI
unnamed: D205.CKO, D206.CKI
unnamed: D205.SDO, D206.SDI
unnamed: D206.CKO, D207.CKI
unnamed: D206.SDO, D207.SDI
unnamed: D207.CKO, D208.CKI
unnamed: D207.SDO, D208.SDI
unnamed: D209.CKO, D210.CKI
unnamed: D209.SDO, D210.SDI
unnamed: D211.CKO, D212.CKI
unnamed: D211.SDO, D212.SDI
unnamed: D212.CKO, D213.CKI
unnamed: D212.SDO, D213.SDI
unnamed: D213.CKO, D214.CKI
unnamed: D213.SDO, D214.SDI
unnamed: D214.CKO, D215.CKI
unnamed: D214.SDO, D215.SDI
unnamed: D215.CKO, D216.CKI
unnamed: D215.SDO, D216.SDI
unnamed: D217.CKO, D218.CKI
unnamed: D217.SDO, D218.SDI
unnamed: D218.SDO, D219.SDI
unnamed: D219.CKO, D220.CKI
unnamed: D219.SDO, D220.SDI
unnamed: D218.CKO, D219.CKI
unnamed: D208.CKO, D209.CKI
unnamed: D208.SDO, D209.SDI
unnamed: D216.SDO, D217.SDI
unnamed: D216.CKO, D217.CKI
unnamed: D221.CKO, D222.CKI
unnamed: D221.SDO, D222.SDI
unnamed: D222.CKO, D223.CKI
unnamed: D222.SDO, D223.SDI
unnamed: D223.CKO, D224.CKI
unnamed: D223.SDO, D224.SDI
unnamed: D224.CKO, D225.CKI
unnamed: D224.SDO, D225.SDI
unnamed: D226.CKO, D227.CKI
unnamed: D226.SDO, D227.SDI
unnamed: D227.CKO, D228.CKI
unnamed: D227.SDO, D228.SDI
unnamed: D229.CKO, D230.CKI
unnamed: D229.SDO, D230.SDI
unnamed: D230.CKO, D231.CKI
unnamed: D230.SDO, D231.SDI
unnamed: D231.CKO, D232.CKI
unnamed: D231.SDO, D232.SDI
unnamed: D232.CKO, D233.CKI
unnamed: D232.SDO, D233.SDI
unnamed: D233.CKO, D234.CKI
unnamed: D233.SDO, D234.SDI
unnamed: D234.CKO, D235.CKI
unnamed: D234.SDO, D235.SDI
unnamed: D235.CKO, D236.CKI
unnamed: D235.SDO, D236.SDI
unnamed: D237.CKO, D238.CKI
unnamed: D237.SDO, D238.SDI
unnamed: D238.SDO, D239.SDI
unnamed: D239.CKO, D240.CKI
unnamed: D239.SDO, D240.SDI
unnamed: D238.CKO, D239.CKI
unnamed: D228.CKO, D229.CKI
unnamed: D228.SDO, D229.SDI
unnamed: D236.SDO, D237.SDI
unnamed: D236.CKO, D237.CKI
unnamed: D200.CKO, D201.CKI
unnamed: D200.SDO, D201.SDI
unnamed: D225.CKO, D226.CKI
unnamed: D210.CKO, D211.CKI
unnamed: D210.SDO, D211.SDI
unnamed: D187.CKO, D188.CKI
unnamed: D187.SDO, D188.SDI
unnamed: D225.SDO, D226.SDI
unnamed: D220.CKO, D221.CKI
unnamed: D220.SDO, D221.SDI
unnamed: D241.CKO, D251.CKI
unnamed: D241.SDO, D251.SDI
unnamed: D251.CKO, D252.CKI
unnamed: D251.SDO, D252.SDI
unnamed: D252.CKO, D253.CKI
unnamed: D252.SDO, D253.SDI
unnamed: D253.CKO, D254.CKI
unnamed: D253.SDO, D254.SDI
unnamed: D254.CKO, D255.CKI
unnamed: D254.SDO, D255.SDI
unnamed: D255.CKO, D256.CKI
unnamed: D255.SDO, D256.SDI
unnamed: D256.CKO, D257.CKI
unnamed: D256.SDO, D257.SDI
unnamed: D242.CKI, D258.CKO
unnamed: D242.SDI, D258.SDO
unnamed: D242.CKO, D243.CKI
unnamed: D242.SDO, D243.SDI
unnamed: D243.CKO, D244.CKI
unnamed: D243.SDO, D244.SDI
unnamed: D244.CKO, D245.CKI
unnamed: D244.SDO, D245.SDI
unnamed: D245.CKO, D246.CKI
unnamed: D245.SDO, D246.SDI
unnamed: D246.CKO, D247.CKI
unnamed: D246.SDO, D247.SDI
unnamed: D249.CKO, D250.CKI
unnamed: D249.SDO, D250.SDI
unnamed: D250.SDO, D259.SDI
unnamed: D259.CKO, D260.CKI
unnamed: D259.SDO, D260.SDI
unnamed: D250.CKO, D259.CKI
unnamed: D257.CKO, D258.CKI
unnamed: D257.SDO, D258.SDI
unnamed: D248.SDO, D249.SDI
unnamed: D248.CKO, D249.CKI
unnamed: D261.CKO, D262.CKI
unnamed: D261.SDO, D262.SDI
unnamed: D262.CKO, D263.CKI
unnamed: D262.SDO, D263.SDI
unnamed: D263.CKO, D264.CKI
unnamed: D263.SDO, D264.SDI
unnamed: D264.CKO, D265.CKI
unnamed: D264.SDO, D265.SDI
unnamed: D265.CKO, D266.CKI
unnamed: D265.SDO, D266.SDI
unnamed: D266.CKO, D267.CKI
unnamed: D266.SDO, D267.SDI
unnamed: D267.CKO, D268.CKI
unnamed: D267.SDO, D268.SDI
unnamed: D269.CKO, D270.CKI
unnamed: D269.SDO, D270.SDI
unnamed: D271.CKO, D272.CKI
unnamed: D271.SDO, D272.SDI
unnamed: D272.CKO, D273.CKI
unnamed: D272.SDO, D273.SDI
unnamed: D273.CKO, D274.CKI
unnamed: D273.SDO, D274.SDI
unnamed: D274.CKO, D275.CKI
unnamed: D274.SDO, D275.SDI
unnamed: D275.CKO, D276.CKI
unnamed: D275.SDO, D276.SDI
unnamed: D277.CKO, D278.CKI
unnamed: D277.SDO, D278.SDI
unnamed: D278.SDO, D279.SDI
unnamed: D279.CKO, D280.CKI
unnamed: D279.SDO, D280.SDI
unnamed: D278.CKO, D279.CKI
unnamed: D268.CKO, D269.CKI
unnamed: D268.SDO, D269.SDI
unnamed: D276.SDO, D277.SDI
unnamed: D276.CKO, D277.CKI
unnamed: D281.CKO, D282.CKI
unnamed: D281.SDO, D282.SDI
unnamed: D282.CKO, D283.CKI
unnamed: D282.SDO, D283.SDI
unnamed: D283.CKO, D284.CKI
unnamed: D283.SDO, D284.SDI
unnamed: D284.CKO, D285.CKI
unnamed: D284.SDO, D285.SDI
unnamed: D286.CKO, D287.CKI
unnamed: D286.SDO, D287.SDI
unnamed: D287.CKO, D288.CKI
unnamed: D287.SDO, D288.SDI
unnamed: D289.CKO, D290.CKI
unnamed: D289.SDO, D290.SDI
unnamed: D290.CKO, D291.CKI
unnamed: D290.SDO, D291.SDI
unnamed: D291.CKO, D292.CKI
unnamed: D291.SDO, D292.SDI
unnamed: D292.CKO, D293.CKI
unnamed: D292.SDO, D293.SDI
unnamed: D293.CKO, D294.CKI
unnamed: D293.SDO, D294.SDI
unnamed: D294.CKO, D295.CKI
unnamed: D294.SDO, D295.SDI
unnamed: D295.CKO, D296.CKI
unnamed: D295.SDO, D296.SDI
unnamed: D297.CKO, D298.CKI
unnamed: D297.SDO, D298.SDI
unnamed: D298.SDO, D299.SDI
unnamed: D299.CKO, D300.CKI
unnamed: D299.SDO, D300.SDI
unnamed: D298.CKO, D299.CKI
unnamed: D288.CKO, D289.CKI
unnamed: D288.SDO, D289.SDI
unnamed: D296.SDO, D297.SDI
unnamed: D296.CKO, D297.CKI
unnamed: D260.CKO, D261.CKI
unnamed: D260.SDO, D261.SDI
unnamed: D285.CKO, D286.CKI
unnamed: D270.CKO, D271.CKI
unnamed: D270.SDO, D271.SDI
unnamed: D247.CKO, D248.CKI
unnamed: D247.SDO, D248.SDI
unnamed: D285.SDO, D286.SDI
unnamed: D280.CKO, D281.CKI
unnamed: D280.SDO, D281.SDI
unnamed: D301.CKO, D311.CKI
unnamed: D301.SDO, D311.SDI
unnamed: D311.CKO, D312.CKI
unnamed: D311.SDO, D312.SDI
unnamed: D312.CKO, D313.CKI
unnamed: D312.SDO, D313.SDI
unnamed: D313.CKO, D314.CKI
unnamed: D313.SDO, D314.SDI
unnamed: D314.CKO, D315.CKI
unnamed: D314.SDO, D315.SDI
unnamed: D315.CKO, D316.CKI
unnamed: D315.SDO, D316.SDI
unnamed: D316.CKO, D317.CKI
unnamed: D316.SDO, D317.SDI
unnamed: D302.CKI, D318.CKO
unnamed: D302.SDI, D318.SDO
unnamed: D302.CKO, D303.CKI
unnamed: D302.SDO, D303.SDI
unnamed: D303.CKO, D304.CKI
unnamed: D303.SDO, D304.SDI
unnamed: D304.CKO, D305.CKI
unnamed: D304.SDO, D305.SDI
unnamed: D305.CKO, D306.CKI
unnamed: D305.SDO, D306.SDI
unnamed: D306.CKO, D307.CKI
unnamed: D306.SDO, D307.SDI
unnamed: D309.CKO, D310.CKI
unnamed: D309.SDO, D310.SDI
unnamed: D310.SDO, D319.SDI
unnamed: D319.CKO, D320.CKI
unnamed: D319.SDO, D320.SDI
unnamed: D310.CKO, D319.CKI
unnamed: D317.CKO, D318.CKI
unnamed: D317.SDO, D318.SDI
unnamed: D308.SDO, D309.SDI
unnamed: D308.CKO, D309.CKI
unnamed: D321.CKO, D322.CKI
unnamed: D321.SDO, D322.SDI
unnamed: D322.CKO, D323.CKI
unnamed: D322.SDO, D323.SDI
unnamed: D323.CKO, D324.CKI
unnamed: D323.SDO, D324.SDI
unnamed: D324.CKO, D325.CKI
unnamed: D324.SDO, D325.SDI
unnamed: D325.CKO, D326.CKI
unnamed: D325.SDO, D326.SDI
unnamed: D326.CKO, D327.CKI
unnamed: D326.SDO, D327.SDI
unnamed: D327.CKO, D328.CKI
unnamed: D327.SDO, D328.SDI
unnamed: D329.CKO, D330.CKI
unnamed: D329.SDO, D330.SDI
unnamed: D331.CKO, D332.CKI
unnamed: D331.SDO, D332.SDI
unnamed: D332.CKO, D333.CKI
unnamed: D332.SDO, D333.SDI
unnamed: D333.CKO, D334.CKI
unnamed: D333.SDO, D334.SDI
unnamed: D334.CKO, D335.CKI
unnamed: D334.SDO, D335.SDI
unnamed: D335.CKO, D336.CKI
unnamed: D335.SDO, D336.SDI
unnamed: D337.CKO, D338.CKI
unnamed: D337.SDO, D338.SDI
unnamed: D338.SDO, D339.SDI
unnamed: D339.CKO, D340.CKI
unnamed: D339.SDO, D340.SDI
unnamed: D338.CKO, D339.CKI
unnamed: D328.CKO, D329.CKI
unnamed: D328.SDO, D329.SDI
unnamed: D336.SDO, D337.SDI
unnamed: D336.CKO, D337.CKI
unnamed: D341.CKO, D342.CKI
unnamed: D341.SDO, D342.SDI
unnamed: D342.CKO, D343.CKI
unnamed: D342.SDO, D343.SDI
unnamed: D343.CKO, D344.CKI
unnamed: D343.SDO, D344.SDI
unnamed: D344.CKO, D345.CKI
unnamed: D344.SDO, D345.SDI
unnamed: D346.CKO, D347.CKI
unnamed: D346.SDO, D347.SDI
unnamed: D347.CKO, D348.CKI
unnamed: D347.SDO, D348.SDI
unnamed: D349.CKO, D350.CKI
unnamed: D349.SDO, D350.SDI
unnamed: D350.CKO, D351.CKI
unnamed: D350.SDO, D351.SDI
unnamed: D351.CKO, D352.CKI
unnamed: D351.SDO, D352.SDI
unnamed: D352.CKO, D353.CKI
unnamed: D352.SDO, D353.SDI
unnamed: D353.CKO, D354.CKI
unnamed: D353.SDO, D354.SDI
unnamed: D354.CKO, D355.CKI
unnamed: D354.SDO, D355.SDI
unnamed: D355.CKO, D356.CKI
unnamed: D355.SDO, D356.SDI
unnamed: D357.CKO, D358.CKI
unnamed: D357.SDO, D358.SDI
unnamed: D358.SDO, D359.SDI
unnamed: D359.CKO, D360.CKI
unnamed: D359.SDO, D360.SDI
unnamed: D358.CKO, D359.CKI
unnamed: D348.CKO, D349.CKI
unnamed: D348.SDO, D349.SDI
unnamed: D356.SDO, D357.SDI
unnamed: D356.CKO, D357.CKI
unnamed: D320.CKO, D321.CKI
unnamed: D320.SDO, D321.SDI
unnamed: D345.CKO, D346.CKI
unnamed: D330.CKO, D331.CKI
unnamed: D330.SDO, D331.SDI
unnamed: D307.CKO, D308.CKI
unnamed: D307.SDO, D308.SDI
unnamed: D345.SDO, D346.SDI
unnamed: D340.CKO, D341.CKI
unnamed: D340.SDO, D341.SDI

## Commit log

2018-10-12 adding silk
2018-10-15 post checklist
2018-10-22 cleaning up schematic
2018-10-22 updating for checklist
2018-10-22 fixing library issue
2018-11-28 updating to proper 6-pin footprint
2018-12-06 version number change
2018-12-07 panel
2018-12-19 production saved over the original design with a panel. Changed back to the original design
2019-01-10 Examples
2019-01-17 adding readme
